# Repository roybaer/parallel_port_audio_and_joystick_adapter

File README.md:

# Parallel port audio and joystick adapter

These are KiCAD and Inkscape design files for an improved FTL Sound Adapter compatible parallel port audio and joystick adapter.

This particular design adds series resistors to prevent a joystick connected to the expansion port from shorting out parallel port lines.

## Photo

## License

This work is licensed under the Creative Commons Attribution-ShareAlike 4.0 International License. To view a copy of this license, visit http://creativecommons.org/licenses/by-sa/4.0/ or send a letter to Creative Commons, PO Box 1866, Mountain View, CA 94042, USA.

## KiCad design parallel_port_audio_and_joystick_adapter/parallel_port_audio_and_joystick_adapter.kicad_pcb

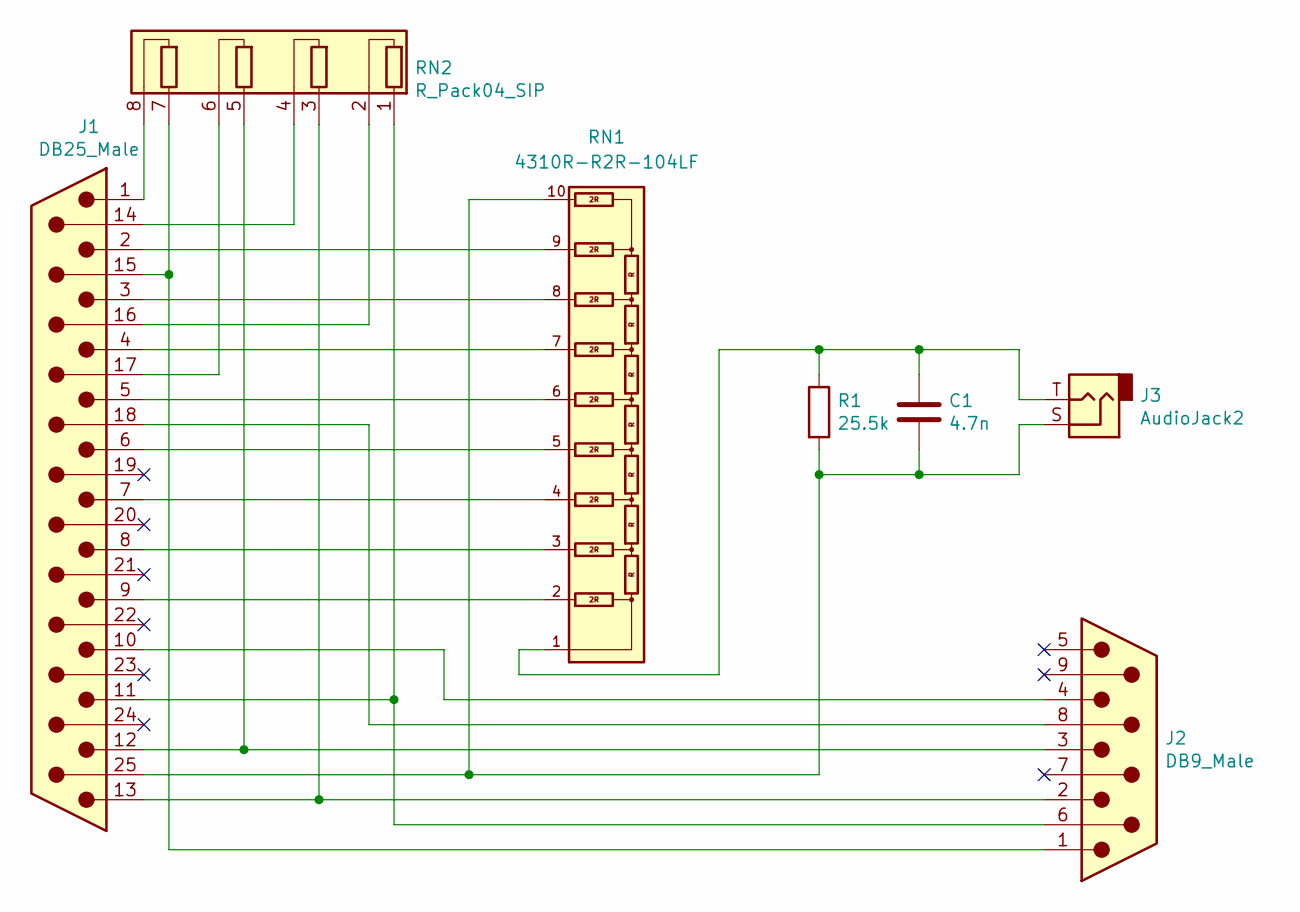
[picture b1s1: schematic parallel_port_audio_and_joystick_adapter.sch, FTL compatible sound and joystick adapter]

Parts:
C1: 4.7n; C_Disc_D4.3mm_W1.9mm_P5.00mm
J1: DB25_Male; DSUB-25_Male_EdgeMount_P2.77mm
J2: DB9_Male; DSUB-9_Male_EdgeMount_P2.77mm
J3: AudioJack2; Jack_3.5mm_CUI_SJ1-3525N_Horizontal
R1: 25.5k; R_Axial_DIN0309_L9.0mm_D3.2mm_P12.70mm_Horizontal
RN1: 4310R-R2R-104LF; R_Array_SIP10
RN2: R_Pack04_SIP; R_Array_SIP8

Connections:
unnamed: C1.1, J3.T, R1.1, RN1.1
unnamed: C1.2, J1.25, J3.S, R1.2, RN1.10
unnamed: J1.1, RN2.8 (R4.2)
unnamed: J1.2, RN1.9
unnamed: J1.3, RN1.8
unnamed: J1.4, RN1.7
unnamed: J1.5, RN1.6
unnamed: J1.6, RN1.5
unnamed: J1.7, RN1.4
unnamed: J1.8, RN1.3
unnamed: J1.9, RN1.2
unnamed: J1.10, J2.4
unnamed: J1.11, J2.6, RN2.1 (R1.1)
unnamed: J1.12, J2.3, RN2.5 (R3.1)
unnamed: J1.13, J2.2, RN2.3 (R2.1)
unnamed: J1.14, RN2.4 (R2.2)
unnamed: J1.15, J2.1, RN2.7 (R4.1)
unnamed: J1.16, RN2.2 (R1.2)
unnamed: J1.17, RN2.6 (R3.2)
unnamed: J1.18, J2.8

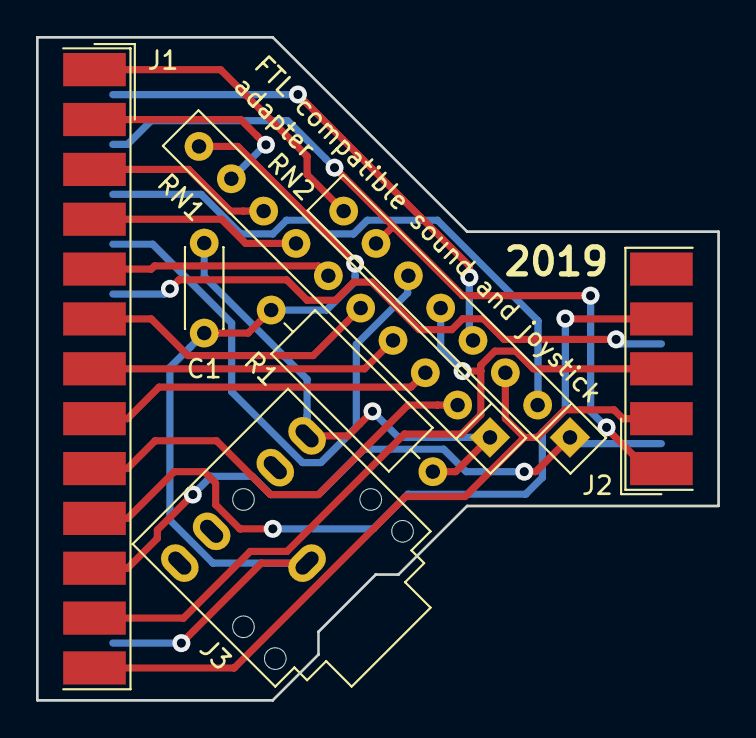
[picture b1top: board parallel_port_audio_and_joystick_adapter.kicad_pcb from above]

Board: 2 copper layers, 37.8 x 36.8 mm, 7 parts (0 on the bottom side), 20 nets.

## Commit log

2019-04-07 add resistors in series to prevent short circuit
2019-05-10 move traces further away from holes
2019-10-04 add label
2019-10-04 add README and photo
